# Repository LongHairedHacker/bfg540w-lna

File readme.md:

BFG 540W LNA
============
A low noise amplifier for NOAA satellite APT signals.

Original design by **YU1AW**
Refer to his [documentation](http://www.qsl.net/yu1aw/LNA/bfp196peng.htm)
for additional information and tips for tuning.

See [plot/lna.pdf](plot/lna.pdf) for the schematic and [parts.md](parts.md) for the BOM.

PCB
---

Results
--------

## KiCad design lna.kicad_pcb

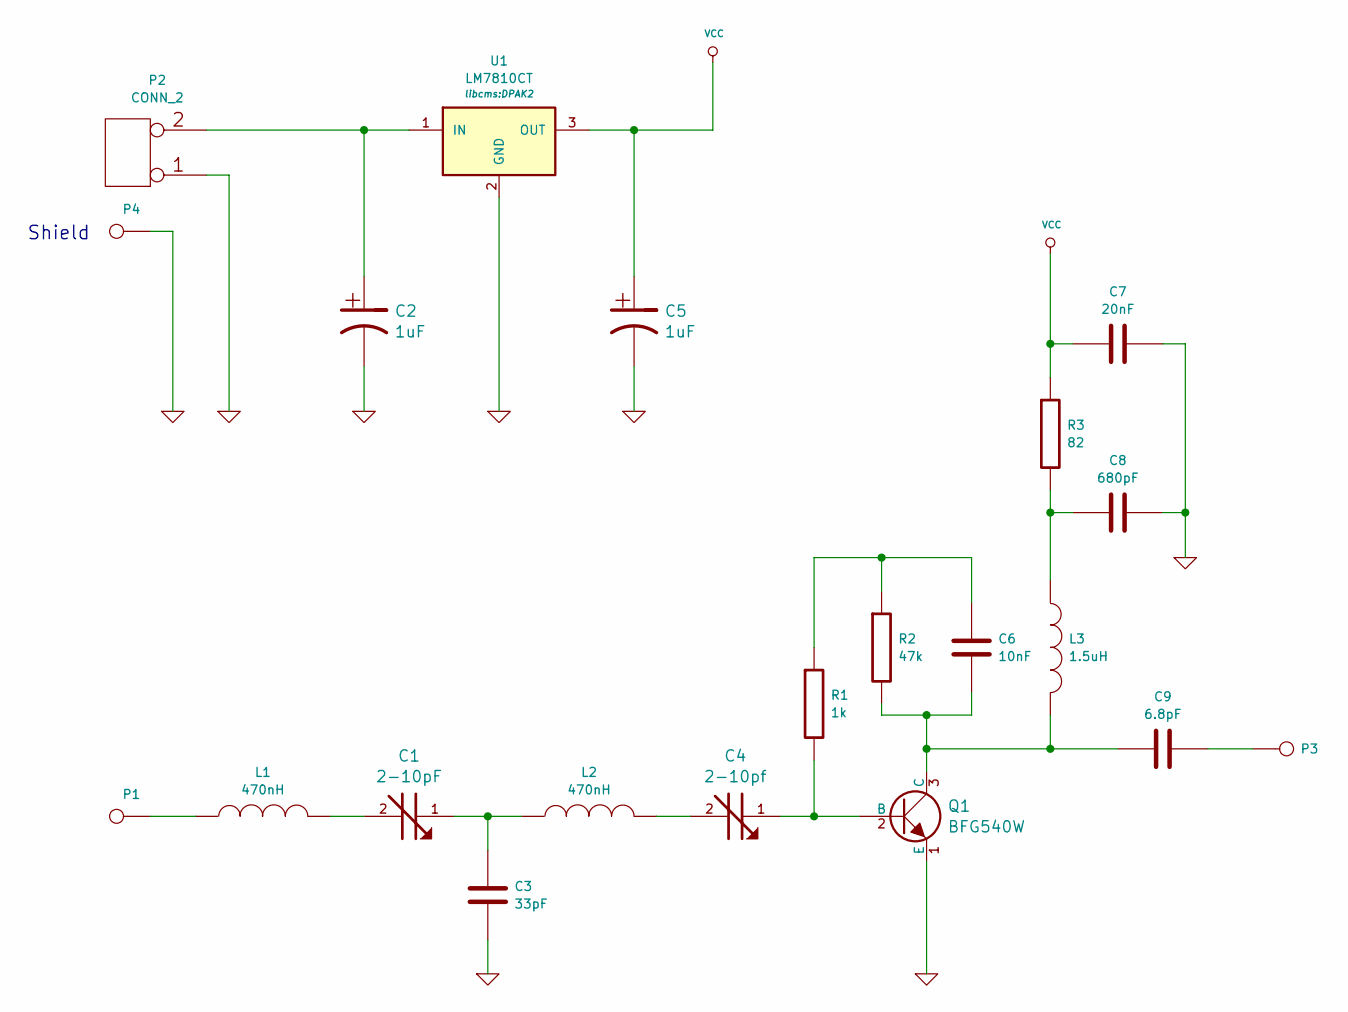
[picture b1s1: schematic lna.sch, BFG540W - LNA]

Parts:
C1: 2-10pF; TZC3
C2, C5: 1uF; c_elec_4x4.5
C3: 33pF; SM0603
C4: 2-10pf; TZC3
C6: 10nF; SM0603
C7: 20nF; SM0603
C8: 680pF; SM0603
C9: 6.8pF; SM0603
L1, L2: 470nH; SM1008
L3: 1.5uH; SM0805
P1, P3: CONN_1; 1pin
P2: CONN_2; SIL-2
P4: CONN_1; Shield
Q1: BFG540W; sot143B
R1: 1k; SM0603
R2: 47k; SM0603
R3: 82; SM0603
U1: LM7810CT; DPAK2

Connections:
GND: C2.2, C3.2, C5.2, C7.1, C8.1, P2.1, P4.1, Q1.1 (E), U1.2 (GND)
unnamed: C1.1, C3.1, L2.1
unnamed: C1.2, L1.2
unnamed: C2.1, P2.2 (PM), U1.1 (IN)
unnamed: C4.1, Q1.2 (B), R1.2
unnamed: C4.2, L2.2
unnamed: C6.1, R1.1, R2.1
unnamed: C6.2, C9.2, L3.2, Q1.3 (C), R2.2
unnamed: C8.2, L3.1, R3.2
unnamed: C9.1, P3.1
unnamed: L1.1, P1.1
VCC: C5.1, C7.2, R3.1, U1.3 (OUT)

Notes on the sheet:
Shield

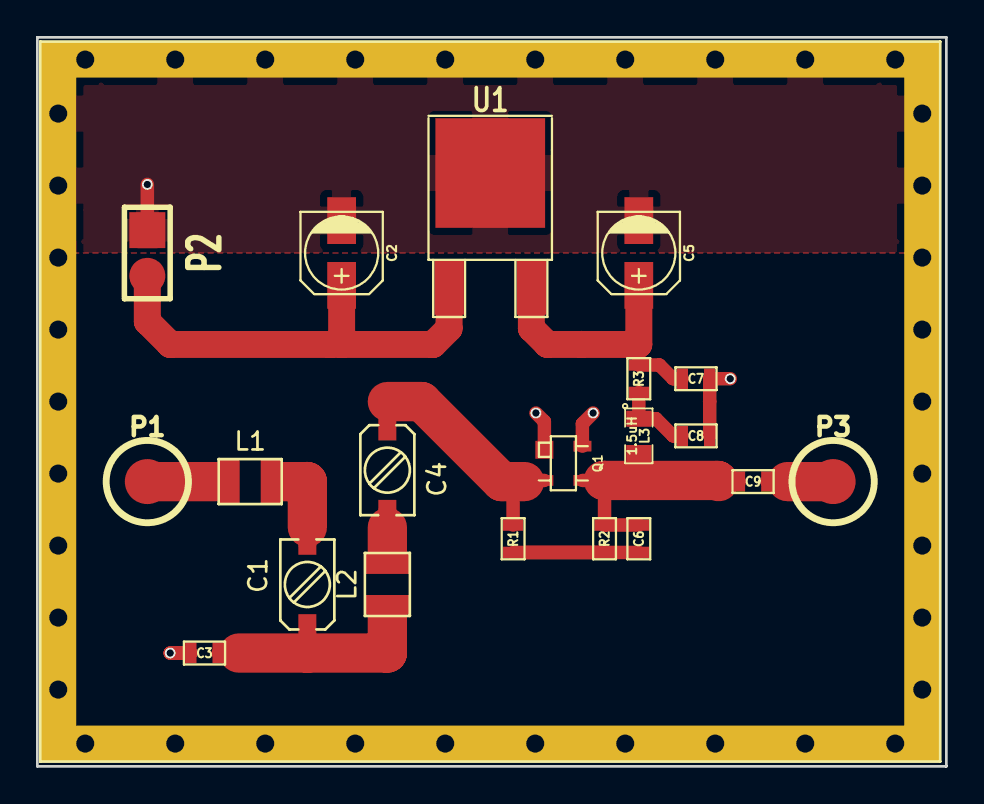
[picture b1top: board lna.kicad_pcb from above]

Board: 2 copper layers, 50.5 x 40.5 mm, 21 parts (0 on the bottom side), 12 nets.

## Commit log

2016-02-01 First version
2016-02-01 Optimizes the layout
2016-02-01 Those are called LC filters not CL filters ... D'oh
2016-02-03 This might be 50Ohm
2017-09-06 Added docs and gebers
